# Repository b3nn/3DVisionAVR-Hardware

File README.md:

# 3DVisionAVR-Hardware
Hardware design files and info for 3DVisionAVR, a clone for 3D Vision Emitter using IR. This is a hardware implementation to use with Lukis101's [3DVisionAVR](https://github.com/lukis101/3DVisionAVR) code

# Notice
This is at an early stage and may change significantly. It should not be considered a replacement for the official 3D Vision Emitter pyramid. You will likely notice limited range of the IR signal and sync issues. Consider this a work in progress which you can help test and improve

# Design Files
This was designed in Kicad v6 and uses [g200kg's kicad-lib-arduino](https://github.com/g200kg/kicad-lib-arduino) library for the Sparkfun Pro Micro

The main component is an Arduino Pro Micro. This should work fine with a clone version to save a few dollars. However, to make things easy, all items can be purchased via the [Sparkfun Wishlist 167547](https://www.sparkfun.com/wish_lists/167547) for around $50 USD. 

# Breadboarding
The circuit is easy to create on a breadboard.

- Pro Micro PIN 3 is our IR Signal (goes to mosfet Gate)
- Pro Micro PIN 10 is USB Status light (goes to resistor to green led)
- Pro Micro RAW is IR LED Power (goes to positive rail)

Hook up GND on both sides of the Pro Micro to the negative rail. The mosfet source pin goes to GND and the middle drain pin goes to the cathode pin of the IR leds (short leg). Wire Pin 3 from the Pro Micro to the gate on the mosfet and then a pull down 10K resistor (connected to the negative rail). Each IR Led should have the anode (long leg) connected via a 100 ohm resistor to the RAW positive rail. Finally hook up the status LED to the signal on Pin 10 (it might be unlabeled but next to pin 16). 

Also if you are using the VESA sync, that goes into the Pro Micro PIN 2. Point the IR LEDs at your face for best results :-)

# PCB
I'm currently having this PCB fabricated, but all files are here if you would also like to fab your own. This is using common through-hole parts so it can be packaged into an easy to assemble kit.

# Flashing
For steps on compiling and flashing Lukis101's [3DVisionAVR](https://github.com/lukis101/3DVisionAVR) code for this project, view [README-FLASH-FIRMWARE.md](README-FLASH-FIRMWARE.md)

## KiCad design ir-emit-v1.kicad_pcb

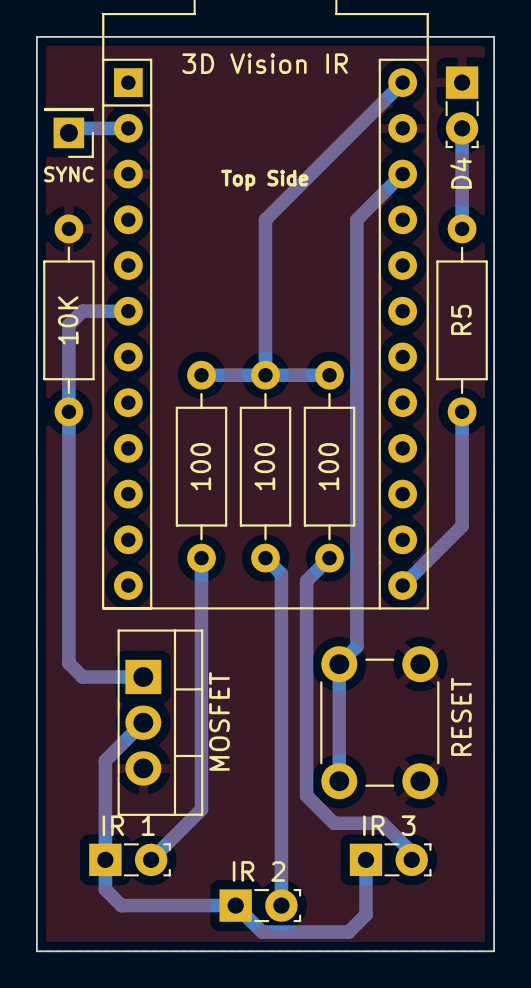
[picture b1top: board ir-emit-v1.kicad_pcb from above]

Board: 2 copper layers, 25.4 x 50.8 mm, 13 parts (0 on the bottom side), 11 nets.

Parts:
3D Vision IR: Sparkfun_Pro_Micro
10K: 10k; R_Axial_DIN0207_L6.3mm_D2.5mm_P10.16mm_Horizontal
100, 100#2, 100#3: 100; R_Axial_DIN0207_L6.3mm_D2.5mm_P10.16mm_Horizontal
D4: LED; LED_SideEmitter_Rectangular_W4.5mm_H1.6mm
IR 1, IR 2, IR 3: IR LED; LED_SideEmitter_Rectangular_W4.5mm_H1.6mm
MOSFET: IRF740; TO-220-3_Vertical
R5: 120; R_Axial_DIN0207_L6.3mm_D2.5mm_P10.16mm_Horizontal
RESET: SW_Push; SW_PUSH_6mm
SYNC: Sync In; PinHeader_1x01_P2.54mm_Vertical

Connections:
+5V: 3D Vision IR.24 (RAW), 100.2, 100#2.2, 100#3.2
GND: 3D Vision IR.3 (GND), 3D Vision IR.23 (GND), 10K.2, D4.1 (K), MOSFET.3 (S), RESET.2
unnamed: IR 1.1 (K), IR 2.1 (K), IR 3.1 (K), MOSFET.2 (D)
unnamed: 100#2.1, IR 1.2 (A)
unnamed: 100.1, IR 2.2 (A)
unnamed: 100#3.1, IR 3.2 (A)
unnamed: D4.2 (A), R5.2
unnamed: 3D Vision IR.6 (~D3), 10K.1, MOSFET.1 (G)
unnamed: 3D Vision IR.13 (~D10/A10), R5.1
unnamed: 3D Vision IR.22 (RST), RESET.1
unnamed: 3D Vision IR.2 (D0/RX), SYNC.1

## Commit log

2022-03-20 Initial upload
2022-03-20 make words better
